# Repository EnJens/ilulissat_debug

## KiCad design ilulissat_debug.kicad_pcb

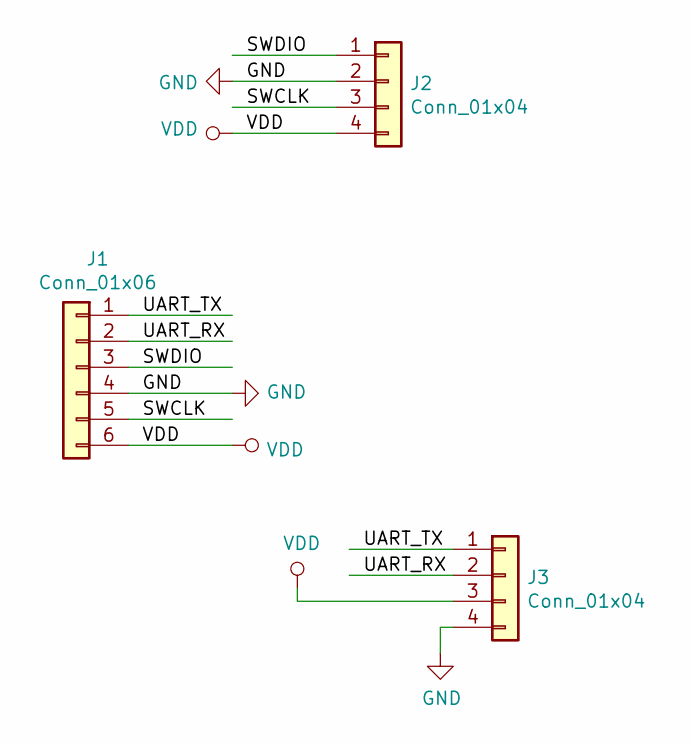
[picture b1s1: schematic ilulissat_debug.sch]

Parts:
J1: Conn_01x06; PinSocket_1x06_P1.27mm_Vertical
J2, J3: Conn_01x04; PinHeader_1x04_P2.54mm_Vertical

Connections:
/SWCLK: J1.5, J2.3
/SWDIO: J1.3, J2.1
/UART_RX: J1.2, J3.2
/UART_TX: J1.1, J3.1
GND: J1.4, J2.2, J3.4
VDD: J1.6, J2.4, J3.3

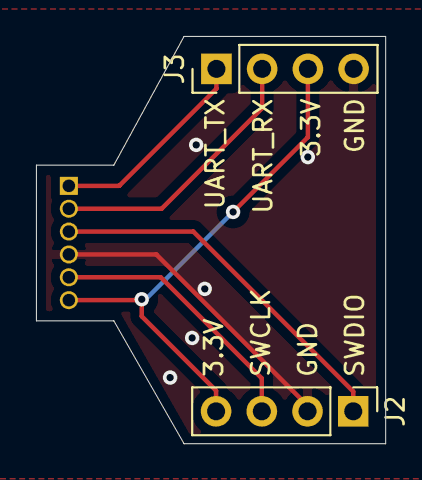
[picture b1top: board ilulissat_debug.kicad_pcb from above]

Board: 2 copper layers, 19.4 x 22.6 mm, 3 parts (1 on the bottom side), 6 nets.

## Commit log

2020-02-16 Trivial debug breakout for 1.27mm header
2020-02-16 Fix silkscreen and orientation of headers
